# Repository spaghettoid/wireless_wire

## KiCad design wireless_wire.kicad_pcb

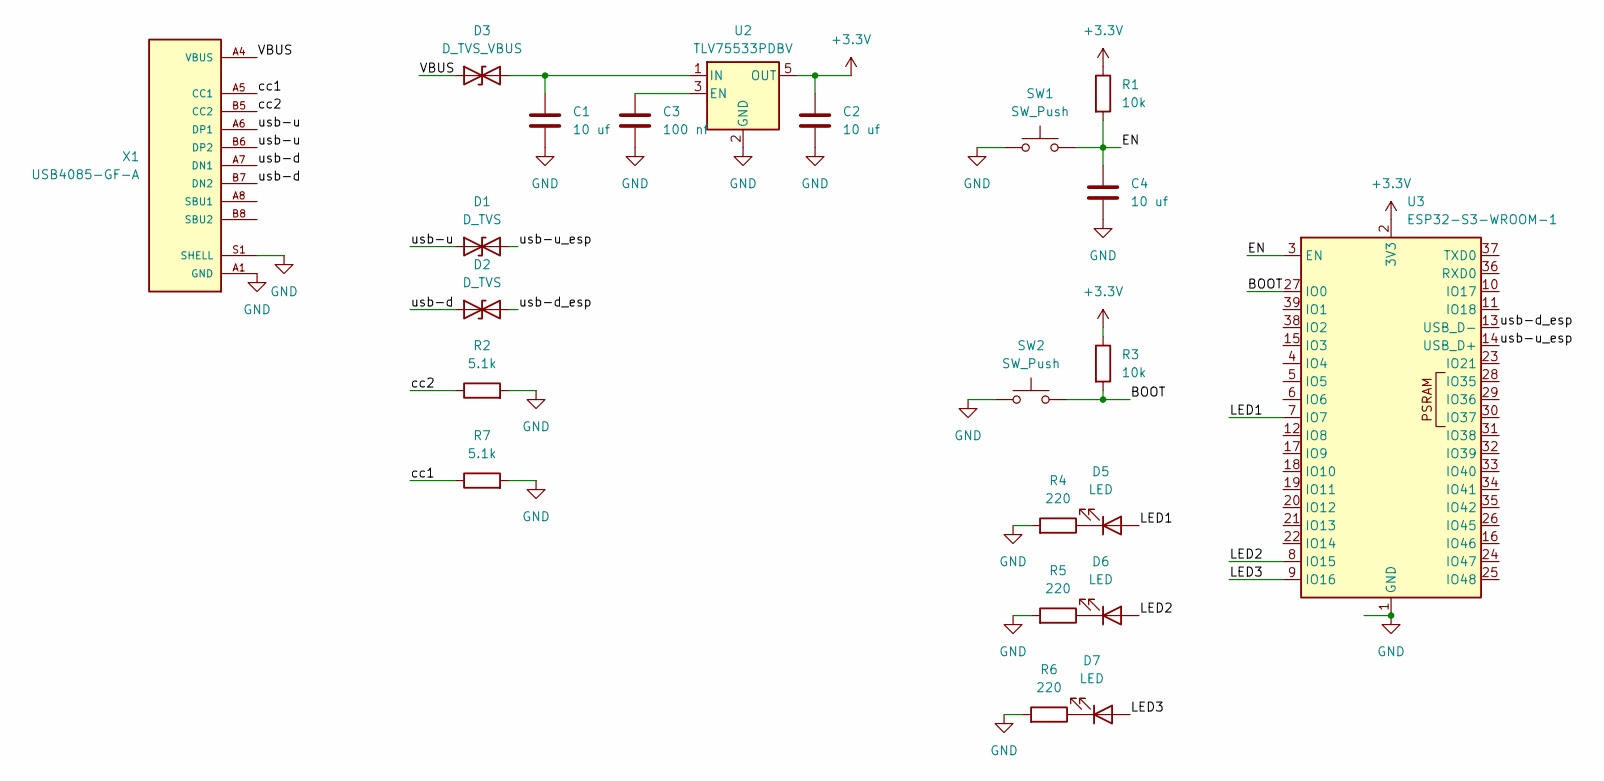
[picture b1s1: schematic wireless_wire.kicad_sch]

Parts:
C1, C2, C4: 10 uf; C_0805_2012Metric
C3: 100 nf; C_0805_2012Metric
D1, D2: D_TVS; D_SOD-323
D3: D_TVS_VBUS; D_SOD-323
D5, D6, D7: LED; LED_0805_2012Metric
R1, R3: 10k; R_0805_2012Metric
R2, R7: 5.1k; R_0805_2012Metric
R4, R5, R6: 220; R_0805_2012Metric
SW1, SW2: SW_Push; SW_SPST_EVQP2_MiddlePushTravel_H2.5mm
U2: TLV75533PDBV; SOT-23-5
U3: ESP32-S3-WROOM-1
X1: USB4085-GF-A; GCT_USB4085-GF-A_REVB

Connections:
+3.3V: C2.1, R1.1, R3.1, U2.5 (OUT), U3.2 (3V3)
/BOOT: R3.2, SW2.2, U3.27 (IO0)
/EN: C4.1, R1.2, SW1.2, U3.3 (EN)
/LED1: D5.2 (A), U3.7 (IO7)
/LED2: D6.2 (A), U3.8 (IO15)
/LED3: D7.2 (A), U3.9 (IO16)
/cc1: R7.1, X1.A5 (CC1)
/cc2: R2.1, X1.B5 (CC2)
/usb-d: D2.1 (A1), X1.A7 (DN1), X1.B7 (DN2)
/usb-d_esp: D2.2 (A2), U3.13 (USB_D-)
/usb-u: D1.1 (A1), X1.A6 (DP1), X1.B6 (DP2)
/usb-u_esp: D1.2 (A2), U3.14 (USB_D+)
GND: C1.2, C2.2, C3.2, C4.2, R2.2, R4.2, R5.2, R6.2, R7.2, SW1.1, SW2.1, U2.2 (GND), U3.1 (GND), U3.40 (GND), U3.41 (GND), X1.A1 (GND), X1.A12 (GND), X1.B1 (GND), X1.B12 (GND), X1.S1 (SHELL), X1.S2 (SHELL), X1.S3 (SHELL), X1.S4 (SHELL)
unnamed: C1.1, D3.2 (A2), U2.1 (IN)
unnamed: D5.1 (K), R4.1
unnamed: D6.1 (K), R5.1
unnamed: D7.1 (K), R6.1
unnamed: C3.1, U2.3 (EN)
VBUS: D3.1 (A1), X1.A4 (VBUS), X1.A9 (VBUS), X1.B4 (VBUS), X1.B9 (VBUS)

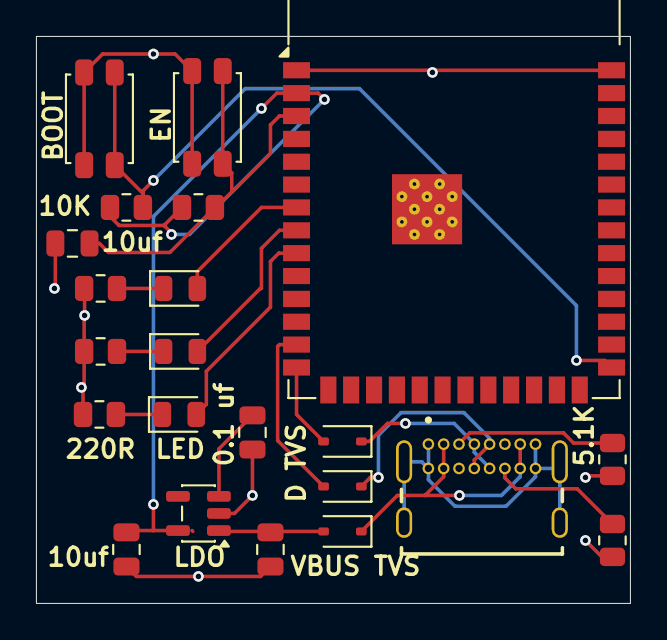
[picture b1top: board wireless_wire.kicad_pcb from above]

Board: 2 copper layers, 33.0 x 31.5 mm, 22 parts (0 on the bottom side), 19 nets.

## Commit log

2026-06-11 initial commit, finished mki expect for silk sceen
2026-06-12 fixed silkscreen and BOM finished
